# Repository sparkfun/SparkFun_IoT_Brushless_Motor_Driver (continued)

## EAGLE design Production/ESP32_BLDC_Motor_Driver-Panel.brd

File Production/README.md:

SparkFun IoT Brushless Motor Driver Production Files
=========================================

These are the production files SparkFun uses for printing PCBs.

License Information
-------------------
This product is open source! 

The hardware is released under [Creative Commons ShareAlike 4.0 International](https://creativecommons.org/licenses/by-sa/4.0/).

Please use, reuse, and modify these files as you see fit. Please maintain attribution to SparkFun Electronics and release anything derivative under the same license.

Distributed as-is; no warranty is given.

- Your friends at SparkFun.

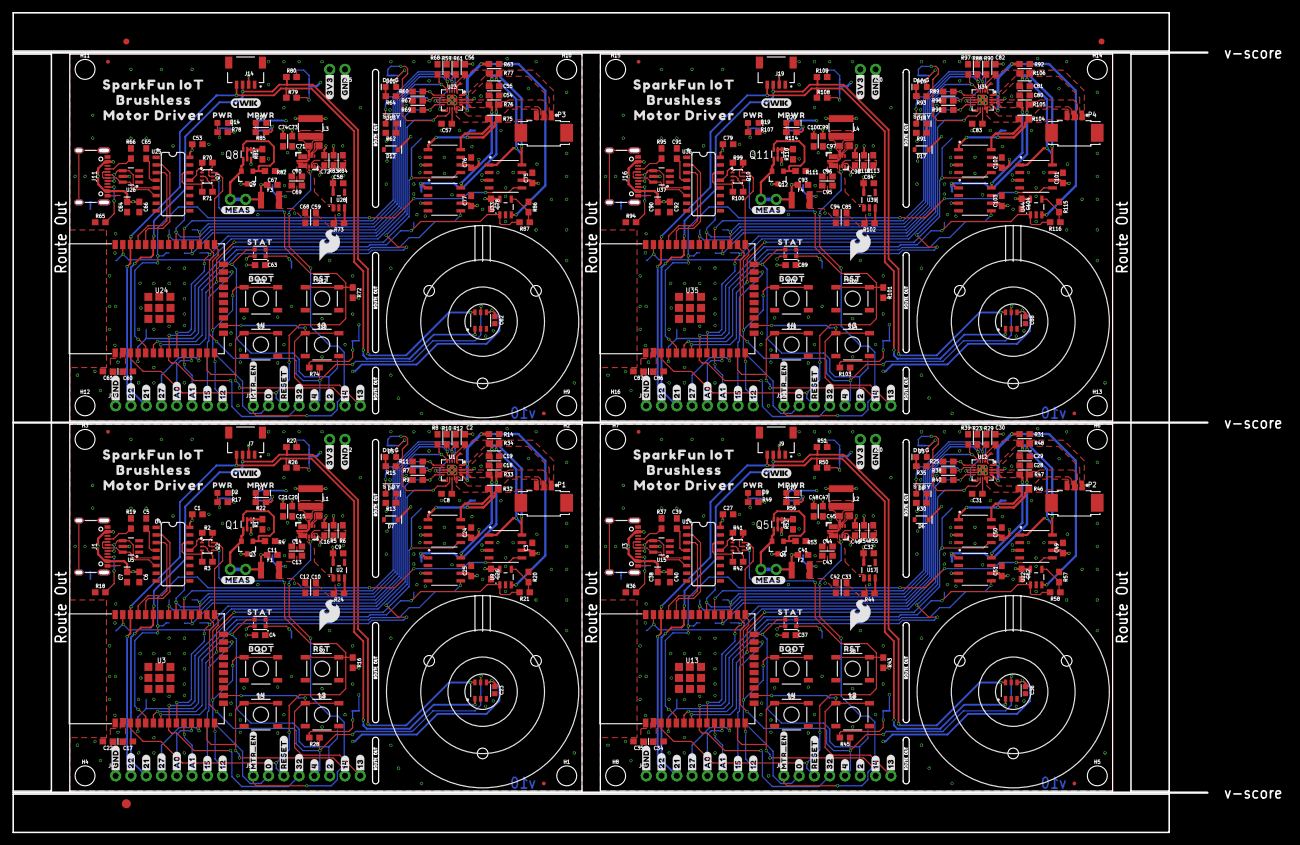
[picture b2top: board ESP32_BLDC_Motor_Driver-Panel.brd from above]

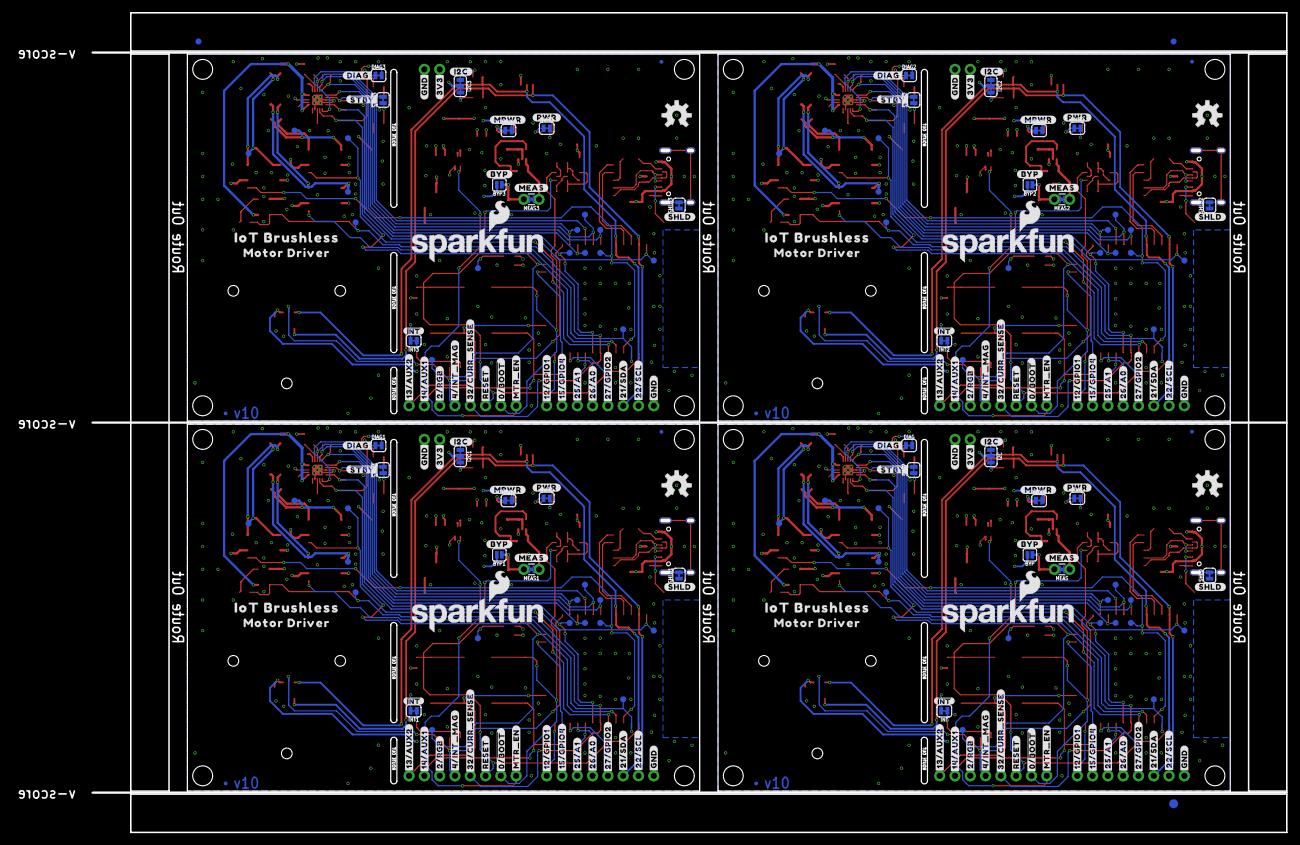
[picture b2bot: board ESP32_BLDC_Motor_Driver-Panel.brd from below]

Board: 4 copper layers, 198.4 x 136.1 mm, 750 parts (235 on the bottom side), 292 nets.

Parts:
!STBY, !STBY1, !STBY2, !STBY3: JUMPER-SMT_2_NC_TRACE_SILK; SMT-JUMPER_2_NC_TRACE_SILK
BYP, BYP1, BYP2, BYP3: JUMPER-SMT_2_NO_SILK; SMT-JUMPER_2_NO_SILK
C1, C2, C3, C4, C6, C8, C11, C12, C15, C17, C19, C24, C25, C26, C27, C29, C30, C31, C34, C37, C40, C41, C42, C45, C49, C50, C51, C52, C53, C55, C56, C57, C60, C63, C66, C67, C68, C71, C75, C76, C77, C78, C79, C81, C82, C83, C86, C89, C92, C93, C94, C97, C101, C102, C103, C104: 0.1uF; 0603
C5, C39, C65, C91: 10nF; 0603
C7, C38, C64, C90: 10uF; 0603-POLAR
C9, C32, C58, C84: 2.2uF; 0603
C10, C33, C59, C85: 1.0uF; 0603
C13, C14, C18, C28, C43, C44, C54, C69, C70, C80, C95, C96: 10uF; 0603
C16, C46, C72, C98: 33pF; 0603
C20, C21, C22, C35, C47, C48, C61, C73, C74, C87, C99, C100: 22uF; 0603
C23, C36, C62, C88: 0.1uF; 0402
D1, D2, D9, D10, D14, D15, D19, D20: RED; LED-0603
D3, D5, D11, D16: GREEN; LED-0603
D4, D8, D13, D18: BLUE; LED-0603
D6, D7, D12, D17: 3.3V; SOD-323
DIAG, DIAG1, DIAG2, DIAG3: JUMPER-SMT_2_NC_TRACE_SILK; SMT-JUMPER_2_NC_TRACE_SILK
E$1, E$2, E$3, E$4: FIDUCIAL-1X2
E$5, E$6: FIDUCIAL-1.5X3
F1, F2, F3, F4: 6V/2A; 1210
FD1, FD2, FD3, FD4, FD5, FD6, FD7, FD8, FD9, FD10, FD11, FD12, FD13, FD14, FD15, FD16: FIDUCIALUFIDUCIAL; FIDUCIAL-MICRO
H1, H2, H3, H4, H5, H6, H7, H8, H9, H10, H11, H12, H13, H14, H15, H16: STAND-OFF
I2C, I2C1, I2C2, I2C3: JUMPER-SMT_3_2-NC_TRACE_SILK; SMT-JUMPER_3_2-NC_TRACE_SILK
INT, INT1, INT2, INT3: JUMPER-SMT_2_NC_TRACE_SILK; SMT-JUMPER_2_NC_TRACE_SILK
J1, J3, J11, J16: USB-C Connector; USB-C-16P_4LAYER-PADS
J2, J10, J15, J20: 1X02_NO_SILK
J4, J6, J12, J17: Breadboard Connector; 1X08_NO_SILK
J5, J8, J13, J18: Breadboard Headers; 1X08_NO_SILK
J7, J9, J14, J19: QWIIC_RIGHT_ANGLE; JST04_1MM_RA
L1, L2, L3, L4: 4.7μH; INDUCTOR_4X4MM
LOGO1, LOGO8, LOGO12, LOGO16: SFE_LOGO_NAMEBLANK; BLANK
LOGO2, LOGO5, LOGO9, LOGO13: OSHW-LOGOM; OSHW-LOGO-M
LOGO3, LOGO6, LOGO10, LOGO14: SFE_LOGO_FLAME.2_INCH; SFE_LOGO_FLAME_.2
LOGO4, LOGO7, LOGO11, LOGO15: QWIIC_LOGO_5MM; QWIIC_5MM
MEAS, MEAS1, MEAS2, MEAS3: JUMPER-COMBO_2_NC_TRACE; COMBO-JUMPER_2_NC_TRACE
MPWR, MPWR1, MPWR2, MPWR3: JUMPER-SMT_2_NC_TRACE_SILK; SMT-JUMPER_2_NC_TRACE_SILK
P1, P2, P3, P4: 0532610371; MOLEX_0532610371
PWR, PWR1, PWR2, PWR3: JUMPER-SMT_2_NC_TRACE_SILK; SMT-JUMPER_2_NC_TRACE_SILK
Q1, Q5, Q8, Q11: SOT363_PHILIPS
Q2, Q4, Q7, Q10: NPN Transistors; SC70-6
Q3, Q6, Q9, Q12: 20V/4.2A/52mΩ/1.4W; SOT23-3
R1, R7, R8, R9, R10, R11, R12, R23, R24, R25, R29, R38, R39, R40, R44, R52, R59, R60, R61, R67, R68, R69, R73, R81, R88, R89, R90, R96, R97, R98, R102, R110: 100k; 0603
R2, R3, R16, R28, R41, R42, R43, R45, R70, R71, R72, R74, R99, R100, R101, R103: 10k; 0603
R4, R53, R82, R111: 1M; 0603
R5, R54, R83, R112: 93.1k; 0603
R6, R55, R84, R113: 30.1k; 0603
R13, R26, R27, R30, R50, R51, R62, R79, R80, R91, R108, R109: 2.2k; 0603
R14, R31, R32, R33, R34, R46, R47, R48, R63, R75, R76, R77, R92, R104, R105, R106: 0.012ohm; 0603
R15, R35, R64, R93: 330; 0603
R17, R22, R49, R56, R78, R85, R107, R114: 4.7k; 0603
R18, R19, R36, R37, R65, R66, R94, R95: 5.1k; 0603
R20, R57, R86, R115: 1k; 0603
R21, R58, R87, R116: 20k; 0603
S1, S2, S3, S4, S5, S6, S7, S8, S9, S10, S11, S12, S13, S14, S15, S16: TACTILE_SWITCH_SMD_5.2MM
SHLD, SHLD1, SHLD2, SHLD3: JUMPER-SMT_2_NC_TRACE_SILK; SMT-JUMPER_2_NC_TRACE_SILK
STAT, STAT1, STAT2, STAT3: WS2812_2020; WS2812-2020
TP1, TP2, TP3, TP4, TP5, TP6, TP7, TP8, TP9, TP10, TP11, TP12, TP13, TP14, TP15, TP16, TP17, TP18, TP19, TP20, TP21, TP22, TP23, TP24, TP25, TP26, TP27, TP28, TP29, TP30, TP31, TP32, TP33, TP34, TP35, TP36, TP37, TP38, TP39, TP40, TP41, TP42, TP43, TP44, TP45, TP46, TP47, TP48, TP49, TP50, TP51, TP52, TP53, TP54, TP55, TP56, TP57, TP58, TP59, TP60: TEST-POINT3X4; PAD.03X.04
U1, U12, U23, U34: TMC6300; QFN-20
U2, U17, U28, U39: 3.3V; SOT23-5
U3, U13, U24, U35: ESP-WROOM-3232D; ESP-WROOM-32D
U4, U14, U25, U36: CH340C; SO016
U5, U15, U26, U37: ESD Diode; SOT-23-6
U6, U18, U29, U40: AP63357; V-DFN3020-13
U7, U10, U11, U19, U20, U21, U30, U31, U32, U41, U42, U43: INA240A1; D8_TEX
U8, U16, U27, U38: TMAG5273; SOT23-6_DBV_TEX
U9, U22, U33, U44: OPA344; SOT23-5
U$1, U$61, U$127, U$190: ORDERING_INSTRUCTIONS
U$2, U$70, U$133, U$196: OT-EM3215
U$3, U$103, U$166, U$229: 1436
U$4, U$71, U$134, U$197: STAT1630063003522
U$5, U$72, U$135, U$198: RST1630063003525
U$6, U$100, U$163, U$226: #14#AUX1#36
U$7, U$89, U$152, U$215: #12#31
U$8, U$119, U$182, U$245: #DIAG#15
U$9, U$101, U$164, U$227: #14#36
U$10, U$120, U$183, U$246: ##STBY##16
U$11, U$73, U$136, U$199: BOOT21630063003532
U$12, U$74, U$137, U$200: PWR21630063003533
U$13, U$113, U$176, U$239: #MTR_EN#131458
U$14, U$15, U$90, U$91, U$153, U$154, U$216, U$217: #GND#32
U$16, U$58, U$122, U$124, U$185, U$187, U$248, U$250: #3V3#18
U$17, U$75, U$138, U$201: #4#INT_MAG#21630063003534
U$18, U$92, U$155, U$218: #22#33
U$19, U$93, U$156, U$219: #21#33
U$20, U$115, U$178, U$241: #MPWR#131468
U$21, U$94, U$157, U$220: #27#33
U$22, U$95, U$158, U$221: #15#33
U$23, U$65, U$128, U$191: #I2C#630063003467
U$24, U$66, U$129, U$192: #SHLD#630063003467
U$25, U$67, U$130, U$193: ##INT#630063003473
U$26, U$76, U$139, U$202: #32#CURR_SENSE#10
U$27, U$77, U$140, U$203: #PWR#33
U$28, U$60, U$121, U$125, U$184, U$188, U$247, U$251: #GND#17
U$29, U$30, U$78, U$79, U$141, U$142, U$204, U$205: #RESET#34
U$31, U$96, U$159, U$222: #0#33
U$32, U$126, U$189, U$252: #0##BOOT##0
U$33, U$97, U$160, U$223: #32#33
U$34, U$98, U$161, U$224: #4#33
U$35, U$80, U$143, U$206: #12#GPIO1#4
U$36, U$99, U$162, U$225: #2#33
U$37, U$81, U$144, U$207: #15#GPIO4#13
U$38, U$102, U$165, U$228: #13#36
U$39, U$104, U$167, U$230: 131437
U$40, U$86, U$149, U$212: #26#A0#30
U$41, U$87, U$150, U$213: #25#A1#30
U$42, U$88, U$151, U$214: #A1#30
U$43, U$105, U$168, U$231: #BYP#131439
U$44, U$106, U$169, U$232: SPARKFUN_IOT131442
U$45, U$68, U$131, U$194: SFE_LOGO_NAME_FLAME_.2
U$46, U$107, U$170, U$233: BRUSHLESS131445
U$47, U$108, U$171, U$234: MOTOR_DRIVER131446
U$48, U$50, U$110, U$111, U$173, U$174, U$236, U$237: #MEAS#131453
U$49, U$109, U$172, U$235: MPWR131449
U$51, U$114, U$177, U$240: #MTR_EN#131460
U$52, U$118, U$181, U$244: #13#AUX2#14
U$53, U$117, U$180, U$243: #STBY#131470
U$54, U$82, U$145, U$208: #27#GPIO2#27
U$55, U$112, U$175, U$238: IOT_BRUSHLESS131454
U$56, U$83, U$146, U$209: #21#SDA#29
U$57, U$116, U$179, U$242: DIAG131469
U$59, U$123, U$186, U$249: #2#RGB#18
U$62, U$69, U$132, U$195: MOTOR_DRIVER630063003515
U$63, U$84, U$147, U$210: #22#SCL#30
U$64, U$85, U$148, U$211: #A0#30

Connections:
1.8_VOUT: C8.1, U1.13
1.8_VOUT1: C31.1, U12.13
1.8_VOUT2: C57.1, U23.13
1.8_VOUT3: C83.1, U34.13
3.3V: C1.1, C3.1, C4.1, C9.1, C17.1, C22.1, C23.1, C24.1, C25.1, C26.1, I2C.2, INT.2, J2.2, J7.2, PWR.2, R16.2, STAT.VCC, U2.5, U3.2, U4.16, U7.3, U7.6, U8.4, U9.5, U10.3, U10.6, U11.3, U11.6
3.3V1: C27.1, C32.1, C34.1, C35.1, C36.1, C37.1, C49.1, C50.1, C51.1, C52.1, I2C1.2, INT1.2, J9.2, J10.2, PWR1.2, R43.2, STAT1.VCC, U13.2, U14.16, U16.4, U17.5, U19.3, U19.6, U20.3, U20.6, U21.3, U21.6, U22.5
3.3V2: C53.1, C58.1, C60.1, C61.1, C62.1, C63.1, C75.1, C76.1, C77.1, C78.1, I2C2.2, INT2.2, J14.2, J15.2, PWR2.2, R72.2, STAT2.VCC, U24.2, U25.16, U27.4, U28.5, U30.3, U30.6, U31.3, U31.6, U32.3, U32.6, U33.5
3.3V3: C79.1, C84.1, C86.1, C87.1, C88.1, C89.1, C101.1, C102.1, C103.1, C104.1, I2C3.2, INT3.2, J19.2, J20.2, PWR3.2, R101.2, STAT3.VCC, U35.2, U36.16, U38.4, U39.5, U41.3, U41.6, U42.3, U42.6, U43.3, U43.6, U44.5
3.3V_A: C2.1, C16.2, C18.1, C19.1, C20.1, C21.1, D7.C, L1.P$2, MPWR.2, R5.2, U1.18
3.3V_A1: C28.1, C29.1, C30.1, C46.2, C47.1, C48.1, D6.C, L2.P$2, MPWR1.2, R54.2, U12.18
3.3V_A2: C54.1, C55.1, C56.1, C72.2, C73.1, C74.1, D12.C, L3.P$2, MPWR2.2, R83.2, U23.18
3.3V_A3: C80.1, C81.1, C82.1, C98.2, C99.1, C100.1, D17.C, L4.P$2, MPWR3.2, R112.2, U34.18
5V: BYP.2, C10.1, C12.1, C13.1, C14.1, F1.2, R24.2, U2.1, U6.P$1
5V1: BYP1.2, C33.1, C42.1, C43.1, C44.1, F2.2, R44.2, U17.1, U18.P$1
5V2: BYP2.2, C59.1, C68.1, C69.1, C70.1, F3.2, R73.2, U28.1, U29.P$1
5V3: BYP3.2, C85.1, C94.1, C95.1, C96.1, F4.2, R102.2, U39.1, U40.P$1
5V_MEAS: MEAS.1, MEAS.3, Q1.4, Q3.2
5V_MEAS1: MEAS1.1, MEAS1.3, Q5.4, Q6.2
5V_MEAS2: MEAS2.1, MEAS2.3, Q8.4, Q9.2
5V_MEAS3: MEAS3.1, MEAS3.3, Q11.4, Q12.2
!RESET: J5.3, Q2.4, R16.1, S2.1, S2.2, U3.3
!RESET1: J8.3, Q4.4, R43.1, S8.1, S8.2, U13.3
!RESET2: J13.3, Q7.4, R72.1, S12.1, S12.2, U24.3
!RESET3: J18.3, Q10.4, R101.1, S16.1, S16.2, U35.3
BST: C15.1, U6.P$6
BST1: C45.1, U18.P$6
BST2: C71.1, U29.P$6
BST3: C97.1, U40.P$6
CH340-RX: U3.35, U4.3
CH340-RX1: U13.35, U14.3
CH340-RX2: U24.35, U25.3
CH340-RX3: U35.35, U36.3
CH340-TX: U3.34, U4.2
CH340-TX1: U13.34, U14.2
CH340-TX2: U24.34, U25.2
CH340-TX3: U35.34, U36.2
D: D5.A, DIAG.1
D1: D3.A, DIAG1.1
D2: D11.A, DIAG2.1
D3: D16.A, DIAG3.1
D+: J1.A6, J1.B6, U4.5, U5.4
D+1: J3.A6, J3.B6, U14.5, U15.4
D+2: J11.A6, J11.B6, U25.5, U26.4
D+3: J16.A6, J16.B6, U36.5, U37.4
D-: J1.A7, J1.B7, U4.6, U5.6
D-1: J3.A7, J3.B7, U14.6, U15.6
D-2: J11.A7, J11.B7, U25.6, U26.6
D-3: J16.A7, J16.B7, U36.6, U37.6
DTR: Q2.1, R2.2, U4.13
DTR1: Q4.1, R41.2, U14.13
DTR2: Q7.1, R70.2, U25.13
DTR3: Q10.1, R99.2, U36.13
ESP_0/QPWR: J5.2, Q2.6, S1.1, S1.2, U3.25
ESP_0/QPWR1: J8.2, Q4.6, S7.1, S7.2, U13.25
ESP_0/QPWR2: J13.2, Q7.6, S11.1, S11.2, U24.25
ESP_0/QPWR3: J18.2, Q10.6, S15.1, S15.2, U35.25
ESP_2/RGB_DI: J5.6, STAT.DI, TP1.1, U3.24
ESP_2/RGB_DI1: J8.6, STAT1.DI, TP27.1, U13.24
ESP_2/RGB_DI2: J13.6, STAT2.DI, TP42.1, U24.24
ESP_2/RGB_DI3: J18.6, STAT3.DI, TP57.1, U35.24
ESP_4/!INT_MAG: J5.5, R28.1, U3.26, U8.5
ESP_4/!INT_MAG1: J8.5, R45.1, U13.26, U16.5
ESP_4/!INT_MAG2: J13.5, R74.1, U24.26, U27.5
ESP_4/!INT_MAG3: J18.5, R103.1, U35.26, U38.5
ESP_5/!STDBY: !STBY.2, U1.11, U3.29
ESP_5/!STDBY1: !STBY1.2, U12.11, U13.29
ESP_5/!STDBY2: !STBY2.2, U23.11, U24.29
ESP_5/!STDBY3: !STBY3.2, U34.11, U35.29
ESP_12/GPIO1: J4.8, U3.14
ESP_12/GPIO2: J6.8, U13.14
ESP_12/GPIO3: J12.8, U24.14
ESP_12/GPIO4: J17.8, U35.14
ESP_13/AUX1: J8.8, S6.1, S6.2, U13.16
ESP_13/AUX2: J5.8, S4.1, S4.2, U3.16
ESP_13/AUX3: J13.8, S10.1, S10.2, U24.16
ESP_13/AUX4: J18.8, S14.1, S14.2, U35.16
ESP_14/AUX1: J5.7, S3.1, S3.2, U3.13
ESP_14/AUX2: J8.7, S5.1, S5.2, U13.13
ESP_14/AUX3: J13.7, S9.1, S9.2, U24.13
ESP_14/AUX4: J18.7, S13.1, S13.2, U35.13
ESP_15/GPIO1: J6.7, U13.23
ESP_15/GPIO2: J12.7, U24.23
ESP_15/GPIO3: J17.7, U35.23
ESP_15/GPIO4: J4.7, U3.23
ESP_16/UH: R12.2, TP3.1, U1.3, U3.27
ESP_16/UH1: R29.2, TP17.1, U12.3, U13.27
ESP_16/UH2: R61.2, TP32.1, U23.3, U24.27
ESP_16/UH3: R90.2, TP47.1, U34.3, U35.27
ESP_17/UL: R11.2, TP4.1, U1.6, U3.28
ESP_17/UL1: R25.2, TP18.1, U12.6, U13.28
ESP_17/UL2: R60.2, TP33.1, U23.6, U24.28
ESP_17/UL3: R89.2, TP48.1, U34.6, U35.28
ESP_18/VH: R10.2, TP5.1, U1.4, U3.30
ESP_18/VH1: R23.2, TP19.1, U12.4, U13.30
ESP_18/VH2: R59.2, TP34.1, U23.4, U24.30
ESP_18/VH3: R88.2, TP49.1, U34.4, U35.30
ESP_19/WH: R8.2, TP7.1, U1.5, U3.31
ESP_19/WH1: R39.2, TP21.1, U12.5, U13.31
ESP_19/WH2: R68.2, TP36.1, U23.5, U24.31
ESP_19/WH3: R97.2, TP51.1, U34.5, U35.31
ESP_21/TP_SDA: J4.3, J7.3, R27.1, U3.33, U8.6
ESP_21/TP_SDA1: J6.3, J9.3, R51.1, U13.33, U16.6
ESP_21/TP_SDA2: J12.3, J14.3, R80.1, U24.33, U27.6
ESP_21/TP_SDA3: J17.3, J19.3, R109.1, U35.33, U38.6
ESP_22/TP_SCL: J4.2, J7.4, R26.1, U3.36, U8.1
ESP_22/TP_SCL1: J6.2, J9.4, R50.1, U13.36, U16.1
ESP_22/TP_SCL2: J12.2, J14.4, R79.1, U24.36, U27.1
ESP_22/TP_SCL3: J17.2, J19.4, R108.1, U35.36, U38.1
ESP_23/VL: R9.2, TP6.1, U1.10, U3.37
ESP_23/VL1: R40.2, TP20.1, U12.10, U13.37
ESP_23/VL2: R69.2, TP35.1, U23.10, U24.37
ESP_23/VL3: R98.2, TP50.1, U34.10, U35.37
ESP_25/TP_A1: J4.6, U3.10
ESP_25/TP_A2: J6.6, U13.10
ESP_25/TP_A3: J12.6, U24.10
ESP_25/TP_A4: J17.6, U35.10
ESP_26/TP_A0: J4.5, U3.11
ESP_26/TP_A1: J6.5, U13.11
ESP_26/TP_A2: J12.5, U24.11
ESP_26/TP_A3: J17.5, U35.11
ESP_27/GPIO1: J6.4, U13.12
ESP_27/GPIO2: J4.4, U3.12
ESP_27/GPIO3: J12.4, U24.12
ESP_27/GPIO4: J17.4, U35.12
ESP_32/CURR_SENSE: J5.4, R21.2, TP9.1, U3.8, U9.1
ESP_32/CURR_SENSE1: J8.4, R58.2, TP23.1, U13.8, U22.1
ESP_32/CURR_SENSE2: J13.4, R87.2, TP38.1, U24.8, U33.1
ESP_32/CURR_SENSE3: J18.4, R116.2, TP53.1, U35.8, U44.1
ESP_33/WL: R7.2, TP8.1, U1.7, U3.9
ESP_33/WL1: R38.2, TP22.1, U12.7, U13.9
ESP_33/WL2: R67.2, TP37.1, U23.7, U24.9
ESP_33/WL3: R96.2, TP52.1, U34.7, U35.9
ESP_34/DIAG: DIAG.2, U1.12, U3.6
ESP_34/DIAG1: DIAG1.2, U12.12, U13.6
ESP_34/DIAG2: DIAG2.2, U23.12, U24.6
ESP_34/DIAG3: DIAG3.2, U34.12, U35.6
ESP_35/U_OUT: TP10.1, U3.7, U7.5
ESP_35/U_OUT1: TP24.1, U13.7, U19.5
ESP_35/U_OUT2: TP39.1, U24.7, U30.5
ESP_35/U_OUT3: TP54.1, U35.7, U41.5
ESP_36/V_OUT: TP11.1, U3.4, U11.5
ESP_36/V_OUT1: TP25.1, U13.4, U21.5
ESP_36/V_OUT2: TP40.1, U24.4, U32.5
ESP_36/V_OUT3: TP55.1, U35.4, U43.5
ESP_39/W_OUT: TP12.1, U3.5, U10.5
ESP_39/W_OUT1: TP26.1, U13.5, U20.5
ESP_39/W_OUT2: TP41.1, U24.5, U31.5
ESP_39/W_OUT3: TP56.1, U35.5, U42.5
FB: C16.1, R5.1, R6.2, U6.P$3
FB1: C46.1, R54.1, R55.2, U18.P$3
FB2: C72.1, R83.1, R84.2, U29.P$3
FB3: C98.1, R112.1, R113.2, U40.P$3
GND: C1.2, C3.2, C4.2, C5.2, C6.2, C7.-, C8.2, C9.2, C10.2, C11.2, C12.2, C13.2, C14.2, C17.2, C18.2, C19.2, C20.2, C21.2, C22.2, C23.2, C24.2, C25.2, C26.2, D1.C, D2.C, D7.A, J1.GND, J1.GND2, J2.1, J4.1, J7.1, R1.1, R4.1, R6.1, R7.1, R8.1, R9.1, R10.1, R11.1, R12.1, R13.1, R14.1, R15.1, R18.1, R19.1, R20.1, S1.3, S1.4, S2.3, S2.4, S3.3, S3.4, S4.3, S4.4, SHLD.1, STAT.GND, U1.8, U1.9, U1.14, U1.PAD, U2.2, U3.1, U3.15, U3.38, U3.GND, U3.GNDT1, U3.GNDT2, U3.GNDT3, U3.GNDT4, U3.GNDT5, U3.GNDT6, U3.GNDT7, U3.GNDT8, U4.1, U5.2, U6.P$4, U6.P$8, U7.2, U7.4, U7.7, U8.2, U8.3, U9.2, U10.2, U10.4, U10.7, U11.2, U11.4, U11.7
GND1: C27.2, C28.2, C29.2, C31.2, C32.2, C33.2, C34.2, C35.2, C36.2, C37.2, C38.-, C39.2, C40.2, C41.2, C42.2, C43.2, C44.2, C47.2, C48.2, C49.2, C50.2, C51.2, C52.2, D6.A, D9.C, D10.C, J3.GND, J3.GND2, J6.1, J9.1, J10.1, R23.1, R25.1, R29.1, R30.1, R31.1, R35.1, R36.1, R37.1, R38.1, R39.1, R40.1, R52.1, R53.1, R55.1, R57.1, S5.3, S5.4, S6.3, S6.4, S7.3, S7.4, S8.3, S8.4, SHLD1.1, STAT1.GND, U12.8, U12.9, U12.14, U12.PAD, U13.1, U13.15, U13.38, U13.GND, U13.GNDT1, U13.GNDT2, U13.GNDT3, U13.GNDT4, U13.GNDT5, U13.GNDT6, U13.GNDT7, U13.GNDT8, U14.1, U15.2, U16.2, U16.3, U17.2, U18.P$4, U18.P$8, U19.2, U19.4, U19.7, U20.2, U20.4, U20.7, U21.2, U21.4, U21.7, U22.2
GND2: C53.2, C54.2, C55.2, C57.2, C58.2, C59.2, C60.2, C61.2, C62.2, C63.2, C64.-, C65.2, C66.2, C67.2, C68.2, C69.2, C70.2, C73.2, C74.2, C75.2, C76.2, C77.2, C78.2, D12.A, D14.C, D15.C, J11.GND, J11.GND2, J12.1, J14.1, J15.1, R59.1, R60.1, R61.1, R62.1, R63.1, R64.1, R65.1, R66.1, R67.1, R68.1, R69.1, R81.1, R82.1, R84.1, R86.1, S9.3, S9.4, S10.3, S10.4, S11.3, S11.4, S12.3, S12.4, SHLD2.1, STAT2.GND, U23.8, U23.9, U23.14, U23.PAD, U24.1, U24.15, U24.38, U24.GND, U24.GNDT1, U24.GNDT2, U24.GNDT3, U24.GNDT4, U24.GNDT5, U24.GNDT6, U24.GNDT7, U24.GNDT8, U25.1, U26.2, U27.2, U27.3, U28.2, U29.P$4, U29.P$8, U30.2, U30.4, U30.7, U31.2, U31.4, U31.7, U32.2, U32.4, U32.7, U33.2
GND3: C79.2, C80.2, C81.2, C83.2, C84.2, C85.2, C86.2, C87.2, C88.2, C89.2, C90.-, C91.2, C92.2, C93.2, C94.2, C95.2, C96.2, C99.2, C100.2, C101.2, C102.2, C103.2, C104.2, D17.A, D19.C, D20.C, J16.GND, J16.GND2, J17.1, J19.1, J20.1, R88.1, R89.1, R90.1, R91.1, R92.1, R93.1, R94.1, R95.1, R96.1, R97.1, R98.1, R110.1, R111.1, R113.1, R115.1, S13.3, S13.4, S14.3, S14.4, S15.3, S15.4, S16.3, S16.4, SHLD3.1, STAT3.GND, U34.8, U34.9, U34.14, U34.PAD, U35.1, U35.15, U35.38, U35.GND, U35.GNDT1, U35.GNDT2, U35.GNDT3, U35.GNDT4, U35.GNDT5, U35.GNDT6, U35.GNDT7, U35.GNDT8, U36.1, U37.2, U38.2, U38.3, U39.2, U40.P$4, U40.P$8, U41.2, U41.4, U41.7, U42.2, U42.4, U42.7, U43.2, U43.4, U43.7, U44.2
MOTOR_EN: J5.1, U6.P$2
MOTOR_EN1: J8.1, U18.P$2
MOTOR_EN2: J13.1, U29.P$2
MOTOR_EN3: J18.1, U40.P$2
unnamed: J1.A5, R19.2
unnamed: C5.1, U4.4
unnamed: J1.B5, R18.2
unnamed: C2.2, U1.2
unnamed: D8.C, R30.2
unnamed: R24.1, U2.3
unnamed: Q2.5, R2.1
unnamed: Q2.2, R3.1
unnamed: D2.A, R17.1
unnamed: D3.C, R35.2
unnamed: INT.1, R28.2
unnamed: I2C.3, R26.2
unnamed: I2C.1, R27.2
unnamed: R20.2, R21.1, U9.4
unnamed: PWR.1, R17.2
unnamed: J3.A5, R37.2
unnamed: BYP.1, C11.1, F1.1, MEAS.2, MEAS.4
unnamed: J3.B5, R36.2
unnamed: C30.2, U12.2
unnamed: Q4.5, R41.1
unnamed: Q1.3, Q3.1, R4.2
unnamed: Q1.1, Q1.2, Q1.5, R1.2
unnamed: Q4.2, R42.1
unnamed: INT1.1, R45.2
unnamed: D9.A, R49.1
unnamed: D1.A, R22.1
unnamed: MPWR.1, R22.2
unnamed: PWR1.1, R49.2
unnamed: D4.C, R13.2
unnamed: R44.1, U17.3
unnamed: C39.1, U14.4
unnamed: I2C1.3, R50.2
unnamed: D5.C, R15.2
unnamed: I2C1.1, R51.2
unnamed: BYP1.1, C41.1, F2.1, MEAS1.2, MEAS1.4
unnamed: Q5.3, Q6.1, R53.2
unnamed: Q5.1, Q5.2, Q5.5, R52.2
unnamed: D10.A, R56.1
unnamed: MPWR1.1, R56.2
unnamed: R57.2, R58.1, U22.4
unnamed: D13.C, R62.2
unnamed: D11.C, R64.2
unnamed: J11.A5, R66.2
unnamed: J11.B5, R65.2
unnamed: C56.2, U23.2
unnamed: Q7.5, R70.1
unnamed: Q7.2, R71.1
unnamed: INT2.1, R74.2
unnamed: D14.A, R78.1
unnamed: PWR2.1, R78.2
unnamed: R73.1, U28.3
unnamed: C65.1, U25.4
unnamed: I2C2.3, R79.2
unnamed: I2C2.1, R80.2
unnamed: BYP2.1, C67.1, F3.1, MEAS2.2, MEAS2.4
unnamed: Q8.3, Q9.1, R82.2
unnamed: Q8.1, Q8.2, Q8.5, R81.2
unnamed: D15.A, R85.1
unnamed: MPWR2.1, R85.2
unnamed: R86.2, R87.1, U33.4
unnamed: D18.C, R91.2
unnamed: D16.C, R93.2
unnamed: J16.A5, R95.2
unnamed: J16.B5, R94.2
unnamed: C82.2, U34.2
unnamed: Q10.5, R99.1
unnamed: Q10.2, R100.1
unnamed: INT3.1, R103.2
unnamed: D19.A, R107.1
unnamed: PWR3.1, R107.2
unnamed: R102.1, U39.3
unnamed: C91.1, U36.4
unnamed: I2C3.3, R108.2
unnamed: I2C3.1, R109.2
unnamed: BYP3.1, C93.1, F4.1, MEAS3.2, MEAS3.4
unnamed: Q11.3, Q12.1, R111.2
unnamed: Q11.1, Q11.2, Q11.5, R110.2
unnamed: D20.A, R114.1
unnamed: MPWR3.1, R114.2
unnamed: R115.2, R116.1, U44.4
RTS: Q2.3, R3.2, U4.14
RTS1: Q4.3, R42.2, U14.14
RTS2: Q7.3, R71.2, U25.14
RTS3: Q10.3, R100.2, U36.14
S: !STBY.1, D4.A
S1: !STBY1.1, D8.A
S2: !STBY2.1, D13.A
S3: !STBY3.1, D18.A
SENSE: R14.2, U1.16, U1.20, U9.3
SENSE1: R31.2, U12.16, U12.20, U22.3
SENSE2: R63.2, U23.16, U23.20, U33.3
SENSE3: R92.2, U34.16, U34.20, U44.3
SENSE_U: R32.1, U1.15, U7.8
SENSE_U1: R46.1, U12.15, U19.8
SENSE_U2: R75.1, U23.15, U30.8
SENSE_U3: R104.1, U34.15, U41.8
SENSE_V: R33.1, U1.17, U11.8
SENSE_V1: R47.1, U12.17, U21.8
SENSE_V2: R76.1, U23.17, U32.8
SENSE_V3: R105.1, U34.17, U43.8
SENSE_W: R34.1, U1.1, U10.8
SENSE_W1: R48.1, U12.1, U20.8
SENSE_W2: R77.1, U23.1, U31.8
SENSE_W3: R106.1, U34.1, U42.8
SHLD: J1.SHLD1, J1.SHLD2, J1.SHLD3, J1.SHLD4, SHLD.2
SHLD1: J3.SHLD1, J3.SHLD2, J3.SHLD3, J3.SHLD4, SHLD1.2
SHLD2: J11.SHLD1, J11.SHLD2, J11.SHLD3, J11.SHLD4, SHLD2.2
SHLD3: J16.SHLD1, J16.SHLD2, J16.SHLD3, J16.SHLD4, SHLD3.2
SW: C15.2, L1.P$1, U6.P$7, U6.P$9
SW1: C45.2, L2.P$1, U18.P$7, U18.P$9
SW2: C71.2, L3.P$1, U29.P$7, U29.P$9
SW3: C97.2, L4.P$1, U40.P$7, U40.P$9
TP1: STAT1.DO, TP16.1
TP2: STAT.DO, TP2.1
TP3: STAT2.DO, TP31.1
TP4: STAT3.DO, TP46.1
U: P1.3, R32.2, TP13.1, U7.1
U1: P2.3, R46.2, TP28.1, U19.1
U2: P3.3, R75.2, TP43.1, U30.1
U3: P4.3, R104.2, TP58.1, U41.1
V: P1.2, R33.2, TP14.1, U11.1
V1: P2.2, R47.2, TP29.1, U21.1
V2: P3.2, R76.2, TP44.1, U32.1
V3: P4.2, R105.2, TP59.1, U43.1
V_USB: C6.1, C7.+, J1.VBUS1, J1.VBUS2, Q1.6, Q3.3, U5.5
V_USB1: C38.+, C40.1, J3.VBUS1, J3.VBUS2, Q5.6, Q6.3, U15.5
V_USB2: C64.+, C66.1, J11.VBUS1, J11.VBUS2, Q8.6, Q9.3, U26.5
V_USB3: C90.+, C92.1, J16.VBUS1, J16.VBUS2, Q11.6, Q12.3, U37.5
W: P1.1, R34.2, TP15.1, U10.1
W1: P2.1, R48.2, TP30.1, U20.1
W2: P3.1, R77.2, TP45.1, U31.1
W3: P4.1, R106.2, TP60.1, U42.1

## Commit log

2023-02-23 Design updates
    Deleted unneeded files folders, continued with designing schematic
2023-02-23 Updates to schematic, added new part
    Continued work with schematic, added more parts to the project/library (TMC6300, output connector for motor, ESP32)
2023-02-27 Added datasheet, further schematic work
    Added datasheet for an IC and continued work on schematic. All sections should now be on the project, need to be checked and completed.
2023-02-28 Design updates
    Committing updates from the day - need much much more work
2023-03-03 Design updates and addition of datasheet
    Added datasheet for new IC on board, continued with design
2023-03-07 Added correct datasheet, continued design
    Continued with design of board, nearing finish of schematic design
2023-03-14 Schematic ready for review
    The schematic has been looked over and is ready for review before starting on the layout. Added Sparkle part number to new library component, added datasheet for new component on board
2023-03-14 Design Updates
    Created new board file, added output connector to motor output in case users want to use a different motor for this board
2023-03-15 Design Review Updates
    Organized file folders, updates from design review - see document for full list of changes. Still needs a little more work before starting fully on the board file
2023-03-16 Added datasheet, further changes from schematic review
    See schematic review for more detailed changes: updated 3.3V LDO for an actual LDO, finished auto-reset circuitry, fixed pinout connections to breakout headers, changed size of logo, added qwiic logo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
2023-03-21 Continue with design
    Adjusted schematic components for better routing. Continued routing design - still a lot left to complete.
2023-03-21 Continued work on layout
    Added polygons to layout, added layers 2,15, continued with routing
2023-03-24 Added new component
    Added library component and datasheet for the magnetic encoder.
2023-03-28 Updates to library and schematic
    Added decoupling caps to ESP32 as per the datasheet, updated the library for the magnetic encoder for better schematic routing, moved components on the board for layout, made small changes/fixes to s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
2023-04-05 Design updates for board and schematic
    Continued work from schematic and layout - not complete, needs more routing and placement adjustments.
2023-04-05 Addition of motor footprint to library; updates to schematic and layout
    Opened up layout of the board for addition of milling layer; broke out power good signal to the breakout headers; adjusted auxilary buttons for proper use; adjusted VIO to be configured correctly; ch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
2023-04-10 Layout Updates
    Completed all air wires and most design rule errors - still a few to go. Layout primarily solidified. logos, name, and labels added to board.
2023-04-18 Design Updates
    Further work done on inline current sensing - restarting computer
2023-04-19 Updates to schematic and layout as per design review checklist
    Finished design errors- close to design review
2023-04-19 Updates for Design Review
    Added more silk for buttons and outputs; added datasheet for correct Op Amp and deleted the old one; adjusted MOLEX output connector to motor for better connectivity and less strain on the cable; cha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
2023-04-21 Design Updates from design review - schematic changes mostly
    ***Changes are still not done*** Changes can be seen detailed in the protos design review; changed TMAG5273 symbol to be correct
2023-04-26 Updates for design review
    Fixed schematic - reordering ESP_32 pinouts, breakout headers, adjusted inline current sensing; re-completed layout - repositioned placement of power scheme and input connectors, swapped placement of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
    For a full list, see design review document
2023-04-28 Design review changes
    Updated datasheets with correct parts in it now; removed power jack; changed direction of motor and output connector to the motor; swapped resistances of op amp for inline current sensing; updated si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
2023-05-01 Design Review Changes
    Added back in AP63557 circuit for more power to motor; Adjusted trace size for better differential pairs and power usage; created standoff board for the motor to sit on while moving; see design notes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
2023-05-01 Final design changes made; files for ordering added
    Made final adjustments with Alex - check document for more information on small adjustments; ran CAM script for output files for board; also made output CAM files for standoff to be ordered as well.
2023-06-08 V10 INITIAL COMMIT
    Added datasheets for new parts; created new library component for the INA240 inline current sensing; lined up other parts for symmetry; redid the OPA344 current sensing section
2023-06-08 Standoff Updates
    Changed the width of the circle for the standoff so there is no friction on the motor when it is spinning. Continued work with layout.
2023-06-09 Reds Review - final changes
    Deleted datasheets no longer needed; updated documents to parts currently on board; added more GND vias to GND return paths on the layout; Fixed the OPA344 op amp section; added decoupling caps to th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
2023-06-14 Changes from Reds Review
    Fixed INA240A1 symbol; changed voltage input range; adjusted OPA344 to be non-inverting; SENSE trace now 30mil instead of 15mil; moved inline current sense resistors to allow kelvin connections; move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
2023-06-15 Updated files for ordering
    Completed all the final requests from the re-review after the reds review; double checked the test points to the test board; updated pcb spacers; updated files for ordering boards
2023-07-05 Updated with Sparkle BOM part change
    No changes to board layout has been made; only a Sparkle part change to U9 due to a retired part.
2023-08-17 Removed uneeded files; renamed standoff to space in file folder
    Removed the op-amp testing schematic and datasheet; renamed Standoff to Spacer for less confusion with ordering/following along
2023-09-08 Move production folder
2023-09-08 Add QR codes
    - Product Page
    - Hookup Guide
2023-09-08 Fix instructions in intial commit
2023-09-18 Update README.md
    Fix tab/space indentation
2023-09-20 Update hardware_overview.md
    Remove banner
2023-09-20 Update mkdocs.yml
    Change twitter icon
2023-09-20 Update
    Markdown - Fix carriage return spacing
2023-09-21 Update README.md
    Add directory info
2023-09-21 Update extra.css
    Add new video sizing
2023-09-21 Link product video
2023-09-21 Update README.md
    Fix numbering
2023-09-21 Update resources.md
    Forgot to link additional datasheets
2023-09-21 Update video link
    Product video was updated
2023-10-06 Added new example folder for WiFi example
    Added WiFi example for IoT Motor Driver as per request from above
2023-10-06 Deployed 5d62d73 with MkDocs version: 1.5.3
2024-07-23 Adds workflow files
2024-07-23 Fixes pathing in workflow
2024-07-23 Updates github action to just include the esp32 thing plus c board
2024-07-23 Updates action to include Simple FOC
2024-07-23 Fixes Simple FOC name in github action
2026-06-03 Deployed dc76919 with MkDocs version: 1.6.1
